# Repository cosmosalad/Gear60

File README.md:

[▶ Check Out GearSeries](https://github.com/cosmosalad/GearSeries)<br/>
[프로젝트 과정(kr)](https://blog.naver.com/cosmosalad/223262540878)<br/><br/>

# Gear60<br/>
Gear60 is a 60% multi-layout keyboard based on the rp2040.
<br/>

It's mostly compatible with 60% layout keyboards. Just modify usb and plate to suit your keyboard housing

<br/>

split_hhkb (fdm print)

<br/><br/>

hhkb - B type (sla print)

<br/><br/>

## Layout<br/>

- solder<br/>

<br/><br/>

- hotswap<br/>

<br/><br/>

There is also a [keyboard plate](https://github.com/cosmosalad/Gear60/tree/main/plate).<br/>
[Keyboard case](https://github.com/cosmosalad/Gear60/tree/main/case) corresponding to this layout.<br/>

<br/><br/>

## PCB<br/>
<br/>
<br/><br/><br/>

<br/>
There is a change from the initial pcb design. [More pcb](https://github.com/cosmosalad/Gear60/tree/main/pcb)<br/><br/>
This pcb was made by jlcpcb.([list of pcb parts](https://github.com/cosmosalad/Gear60/blob/main/pcb/hotswap/part%20list.md))<br/><br/>
This pcb prepared the [vial](https://github.com/cosmosalad/Gear60/tree/main/vial) as firmware<br/><br/>

<p align="center">
  
</p>
<br/>

## Reference<br/>
- [keyboard-layout-editor](http://www.keyboard-layout-editor.com/)<br/>
- [Hardware design with RP2040](https://datasheets.raspberrypi.com/rp2040/hardware-design-with-rp2040.pdf?_gl=1*anhmk8*_ga*NTIyODYwMjcuMTcwODI1NDcxMw..*_ga_22FD70LWDS*MTcwODI1NDcxNC4xLjAuMTcwODI1NDcxNC4wLjAuMA..), [Hardware design for the RP2040](https://github.com/Sleepdealr/RP2040-designguide)<br/>
- [kicad](https://www.kicad.org/), [marbastlib](https://github.com/ebastler/marbastlib), [kleeb](https://github.com/crides/kleeb)<br/>
- [KiCAD KLE Placer](https://github.com/zykrah/kicad-kle-placer), [Firmware 'scripts'](https://github.com/zykrah/firmware-scripts)<br/>
- [vial](https://get.vial.today/), [qmk](https://qmk.fm/)<br/>
- [ai03 Plate Generator v2](https://github.com/ai03-2725/yet-another-keyboard-builder)<br/>

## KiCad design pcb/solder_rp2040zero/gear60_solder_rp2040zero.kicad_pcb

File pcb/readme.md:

### Gear60 hotswap<br/>
<br/>

<br/><br/>

### Gear60 solder<br/>
<br/>

<br/><br/>

### Gear60 solder_rp2040zero<br/>
<br/>

<br/><br/>

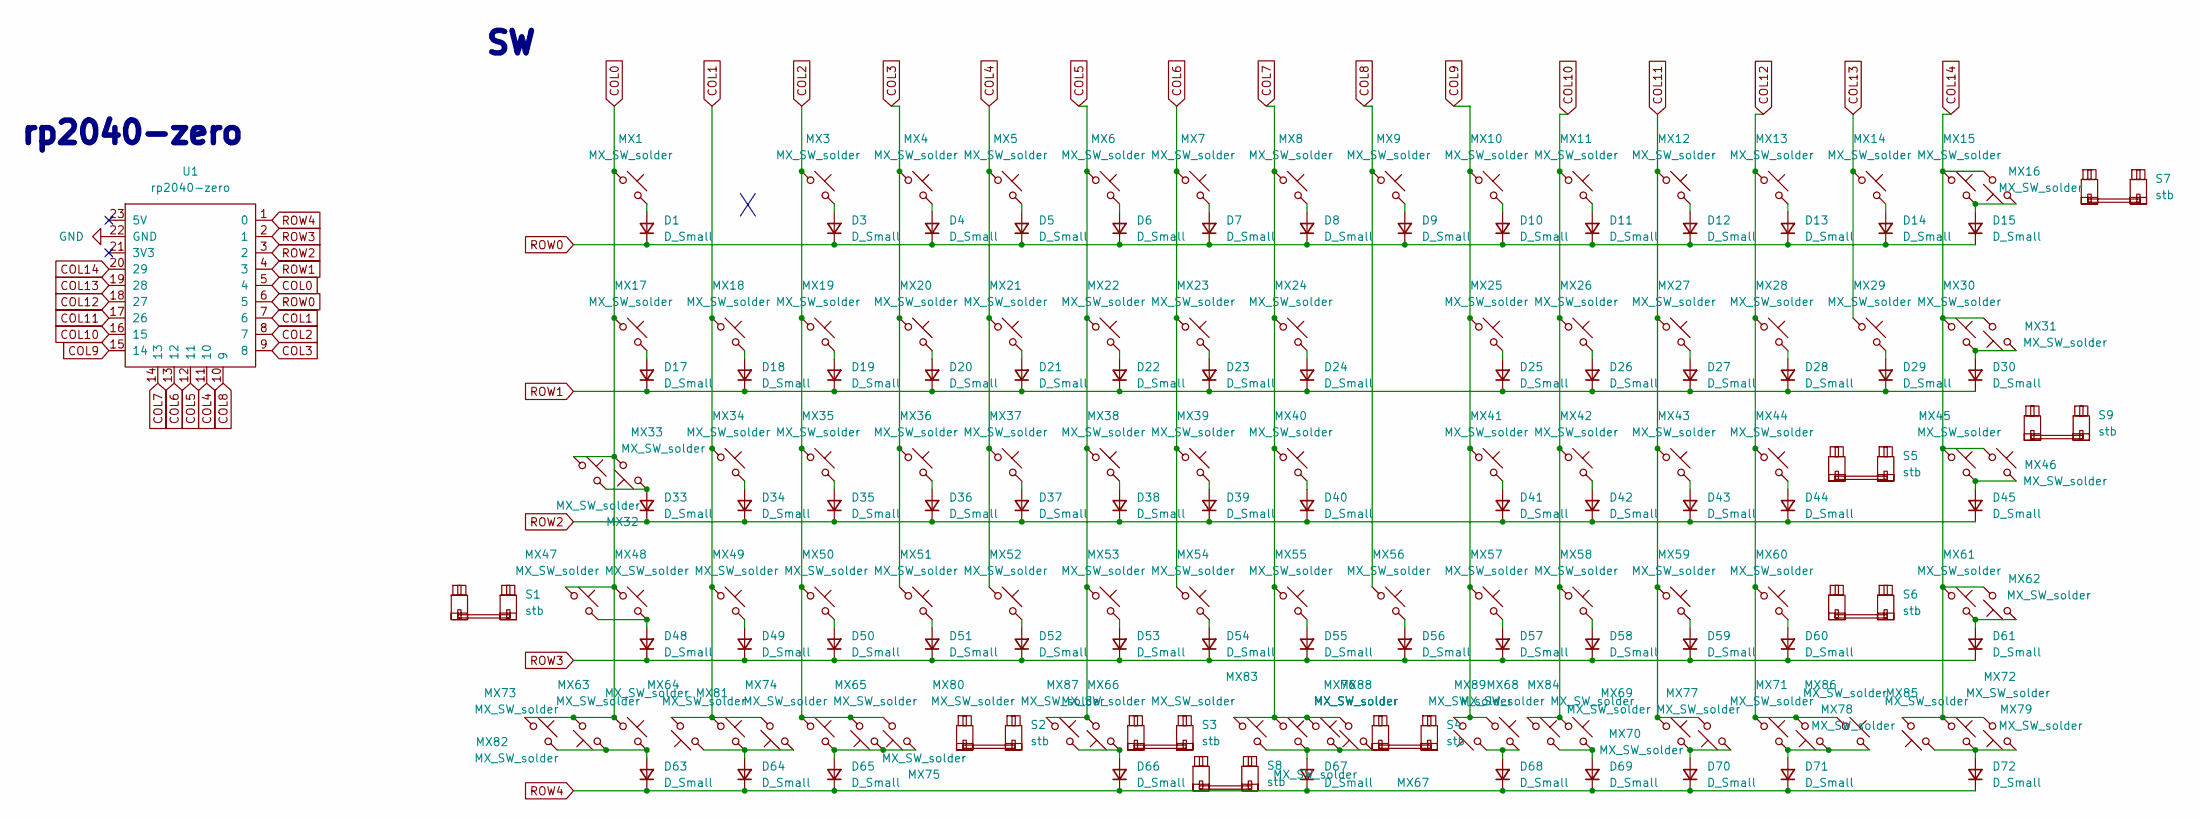
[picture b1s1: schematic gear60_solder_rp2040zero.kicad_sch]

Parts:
D1, D3, D4, D5, D6, D7, D8, D9, D10, D11, D12, D13, D14, D15, D17, D18, D19, D20, D21, D22, D23, D24, D25, D26, D27, D28, D29, D30, D33, D34, D35, D36, D37, D38, D39, D40, D41, D42, D43, D44, D45, D48, D49, D50, D51, D52, D53, D54, D55, D56, D57, D58, D59, D60, D61, D63, D64, D65, D66, D67, D68, D69, D70, D71, D72: D_Small; D_SOD-123
MX1, MX3, MX4, MX5, MX6, MX7, MX8, MX9, MX10, MX11, MX12, MX13, MX14, MX15, MX16, MX18, MX19, MX20, MX21, MX22, MX23, MX24, MX25, MX26, MX27, MX28, MX29, MX31, MX34, MX35, MX36, MX37, MX38, MX39, MX40, MX41, MX42, MX43, MX44, MX45, MX46, MX47, MX49, MX50, MX51, MX52, MX53, MX54, MX55, MX56, MX57, MX58, MX59, MX61, MX62, MX63, MX64, MX66, MX67, MX69, MX70, MX71, MX72, MX74, MX76, MX78, MX83, MX87, MX88, MX89: MX_SW_solder; SW_MX_1u
MX17, MX30, MX73, MX75, MX79: MX_SW_solder; SW_MX_1.5u
MX32: MX_SW_solder; SW_MX_1.75u_STP_1.25
MX33, MX60: MX_SW_solder; SW_MX_1.75u
MX48, MX65, MX68, MX77, MX80, MX81, MX82, MX84, MX85, MX86: MX_SW_solder; SW_MX_1.25u
S1, S3, S5: stb; STAB_MX_P_2.25u
S2, S6: stb; STAB_MX_P_2.75u
S4: stb; STAB_MX_P_7u
S7: stb; STAB_MX_P_2u
S8: stb; STAB_MX_P_6.25u
S9: stb; STAB_MX_ISO
U1: rp2040-zero; rp2040-zero-tht-new_long

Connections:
COL0: MX1.1, MX17.1, MX32.1, MX33.2, MX47.1, MX48.1, MX63.1, MX73.2, MX82.1, U1.5 (4)
COL1: MX18.1, MX34.1, MX49.1, MX64.1, MX74.2, MX81.2, U1.7 (6)
COL2: MX3.1, MX19.1, MX35.1, MX50.1, MX65.1, MX75.2, MX80.2, U1.8 (7)
COL3: MX4.1, MX20.1, MX36.1, MX51.1, U1.9 (8)
COL4: MX5.1, MX21.1, MX37.1, MX52.1, U1.11 (10)
COL5: MX6.1, MX22.1, MX38.1, MX53.1, MX66.2, MX87.1, U1.12 (11)
COL6: MX7.1, MX23.1, MX39.1, MX54.1, U1.13 (12)
COL7: MX8.1, MX24.1, MX40.1, MX55.1, MX67.1, MX76.1, MX83.1, MX88.2, U1.14 (13)
COL8: MX9.1, MX56.1, U1.10 (9)
COL9: MX10.1, MX25.1, MX41.1, MX57.1, MX68.1, MX89.2, U1.15 (14)
COL10: MX11.1, MX26.1, MX42.1, MX58.1, MX69.1, MX84.1, U1.16 (15)
COL11: MX12.1, MX27.1, MX43.1, MX59.1, MX70.1, MX77.2, U1.17 (26)
COL12: MX13.1, MX28.1, MX44.1, MX60.1, MX71.1, MX78.2, MX86.1, U1.18 (27)
COL13: MX14.1, MX29.1, U1.19 (28)
COL14: MX15.1, MX16.2, MX30.1, MX31.2, MX45.1, MX46.1, MX61.1, MX62.2, MX72.1, MX79.2, MX85.2, U1.20 (29)
GND: U1.22 (GND)
unnamed: D1.2 (A), MX1.2
unnamed: D3.2 (A), MX3.2
unnamed: D4.2 (A), MX4.2
unnamed: D5.2 (A), MX5.2
unnamed: D6.2 (A), MX6.2
unnamed: D7.2 (A), MX7.2
unnamed: D8.2 (A), MX8.2
unnamed: D9.2 (A), MX9.2
unnamed: D10.2 (A), MX10.2
unnamed: D11.2 (A), MX11.2
unnamed: D12.2 (A), MX12.2
unnamed: D13.2 (A), MX13.2
unnamed: D14.2 (A), MX14.2
unnamed: D15.2 (A), MX15.2, MX16.1
unnamed: D17.2 (A), MX17.2
unnamed: D18.2 (A), MX18.2
unnamed: D19.2 (A), MX19.2
unnamed: D20.2 (A), MX20.2
unnamed: D21.2 (A), MX21.2
unnamed: D22.2 (A), MX22.2
unnamed: D23.2 (A), MX23.2
unnamed: D24.2 (A), MX24.2
unnamed: D25.2 (A), MX25.2
unnamed: D26.2 (A), MX26.2
unnamed: D27.2 (A), MX27.2
unnamed: D28.2 (A), MX28.2
unnamed: D29.2 (A), MX29.2
unnamed: D30.2 (A), MX30.2, MX31.1
unnamed: D33.2 (A), MX32.2, MX33.1
unnamed: D34.2 (A), MX34.2
unnamed: D35.2 (A), MX35.2
unnamed: D36.2 (A), MX36.2
unnamed: D37.2 (A), MX37.2
unnamed: D38.2 (A), MX38.2
unnamed: D39.2 (A), MX39.2
unnamed: D40.2 (A), MX40.2
unnamed: D41.2 (A), MX41.2
unnamed: D42.2 (A), MX42.2
unnamed: D43.2 (A), MX43.2
unnamed: D44.2 (A), MX44.2
unnamed: D45.2 (A), MX45.2, MX46.2
unnamed: D48.2 (A), MX47.2, MX48.2
unnamed: D49.2 (A), MX49.2
unnamed: D50.2 (A), MX50.2
unnamed: D51.2 (A), MX51.2
unnamed: D52.2 (A), MX52.2
unnamed: D53.2 (A), MX53.2
unnamed: D54.2 (A), MX54.2
unnamed: D55.2 (A), MX55.2
unnamed: D56.2 (A), MX56.2
unnamed: D57.2 (A), MX57.2
unnamed: D58.2 (A), MX58.2
unnamed: D59.2 (A), MX59.2
unnamed: D60.2 (A), MX60.2
unnamed: D61.2 (A), MX61.2, MX62.1
unnamed: D63.2 (A), MX63.2, MX73.1, MX82.2
unnamed: D64.2 (A), MX64.2, MX74.1, MX81.1
unnamed: D65.2 (A), MX65.2, MX75.1, MX80.1
unnamed: D66.2 (A), MX66.1, MX87.2
unnamed: D67.2 (A), MX67.2, MX76.2, MX83.2, MX88.1
unnamed: D68.2 (A), MX68.2, MX89.1
unnamed: D69.2 (A), MX69.2, MX84.2
unnamed: D70.2 (A), MX70.2, MX77.1
unnamed: D71.2 (A), MX71.2, MX78.1, MX86.2
unnamed: D72.2 (A), MX72.2, MX79.1, MX85.1
ROW0: D1.1 (K), D3.1 (K), D4.1 (K), D5.1 (K), D6.1 (K), D7.1 (K), D8.1 (K), D9.1 (K), D10.1 (K), D11.1 (K), D12.1 (K), D13.1 (K), D14.1 (K), D15.1 (K), U1.6 (5)
ROW1: D17.1 (K), D18.1 (K), D19.1 (K), D20.1 (K), D21.1 (K), D22.1 (K), D23.1 (K), D24.1 (K), D25.1 (K), D26.1 (K), D27.1 (K), D28.1 (K), D29.1 (K), D30.1 (K), U1.4 (3)
ROW2: D33.1 (K), D34.1 (K), D35.1 (K), D36.1 (K), D37.1 (K), D38.1 (K), D39.1 (K), D40.1 (K), D41.1 (K), D42.1 (K), D43.1 (K), D44.1 (K), D45.1 (K), U1.3 (2)
ROW3: D48.1 (K), D49.1 (K), D50.1 (K), D51.1 (K), D52.1 (K), D53.1 (K), D54.1 (K), D55.1 (K), D56.1 (K), D57.1 (K), D58.1 (K), D59.1 (K), D60.1 (K), D61.1 (K), U1.2 (1)
ROW4: D63.1 (K), D64.1 (K), D65.1 (K), D66.1 (K), D67.1 (K), D68.1 (K), D69.1 (K), D70.1 (K), D71.1 (K), D72.1 (K), U1.1 (0)

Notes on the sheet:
rp2040-zero

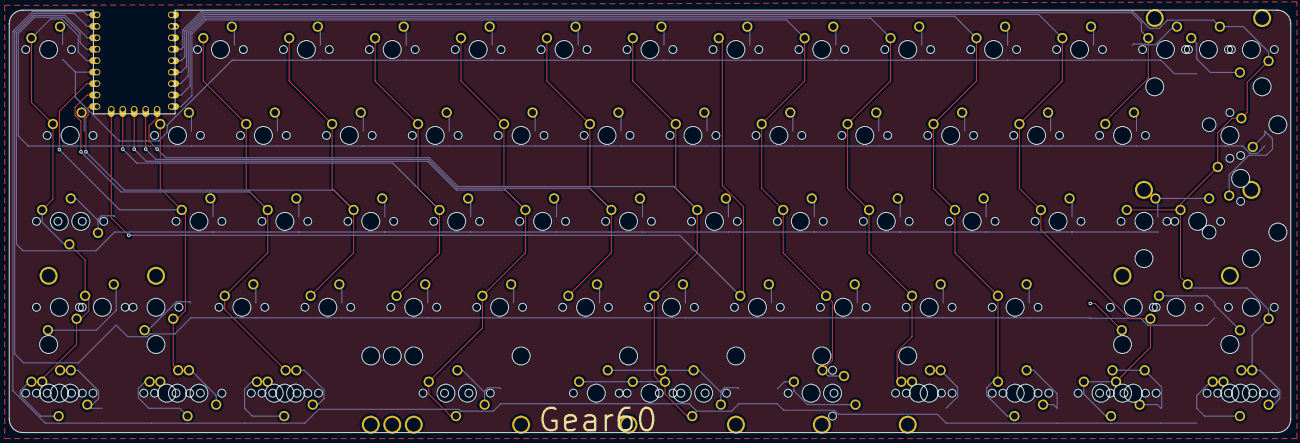
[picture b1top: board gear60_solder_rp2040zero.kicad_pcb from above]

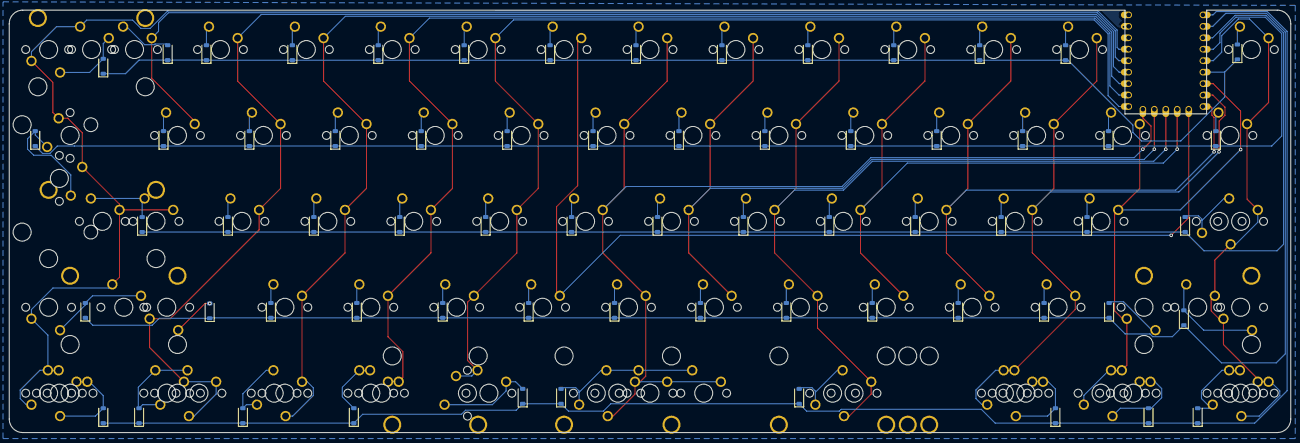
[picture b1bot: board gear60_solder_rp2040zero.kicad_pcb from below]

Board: 2 copper layers, 284.2 x 93.7 mm, 163 parts (66 on the bottom side), 85 nets.

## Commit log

2024-02-18 Create text
2024-02-18 Create t
2024-02-18 Create d
2024-02-18 Rename gear60 plate.stl to gear60_plate.stl
2024-02-18 Create a
2024-02-18 Rename gear60_bottom.stl to bottom.stl
2024-02-18 Rename gear60_top.stl to top.stl
2024-02-18 Rename gear60_top_hhkb.stl to top_hhkb.stl
2024-02-18 Rename gear60_top_wkl.stl to top_wkl.stl
2024-02-18 Rename gear60_top_split_hhkb.stl to top_split_hhkb.stl
2024-02-19 Rename a-type.stl to a-type.stl
2024-02-19 Rename bottom.stl to bottom.stl
2024-02-19 Rename top.stl to top.stl
2024-02-19 Rename top_hhkb.stl to top_hhkb.stl
2024-02-19 Rename top_split_hhkb.stl to top_split_hhkb.stl
2024-02-19 Rename top_split_hhkb_a-type.stl to top_split_hhkb_a-type.stl
2024-02-19 Rename top_wkl.stl to top_wkl.stl
2024-02-19 Rename gear60_hs_gerber.zip to gear60_hs_gerber.zip
2024-02-19 Rename gear60_solder_gerber.zip to gear60_solder_gerber.zip
2024-02-21 Create LICENSE
2024-02-21 Rename gear60_hs_gerber.zip to gear60_solder_gerber.zip
2024-02-21 Rename gear60_vial.uf2 to gear60_vial_hotswap.uf2
2024-03-14 Rename gear60_solder_rp2040zero.uf2 to gear60_vial_rp2040zero.uf2
